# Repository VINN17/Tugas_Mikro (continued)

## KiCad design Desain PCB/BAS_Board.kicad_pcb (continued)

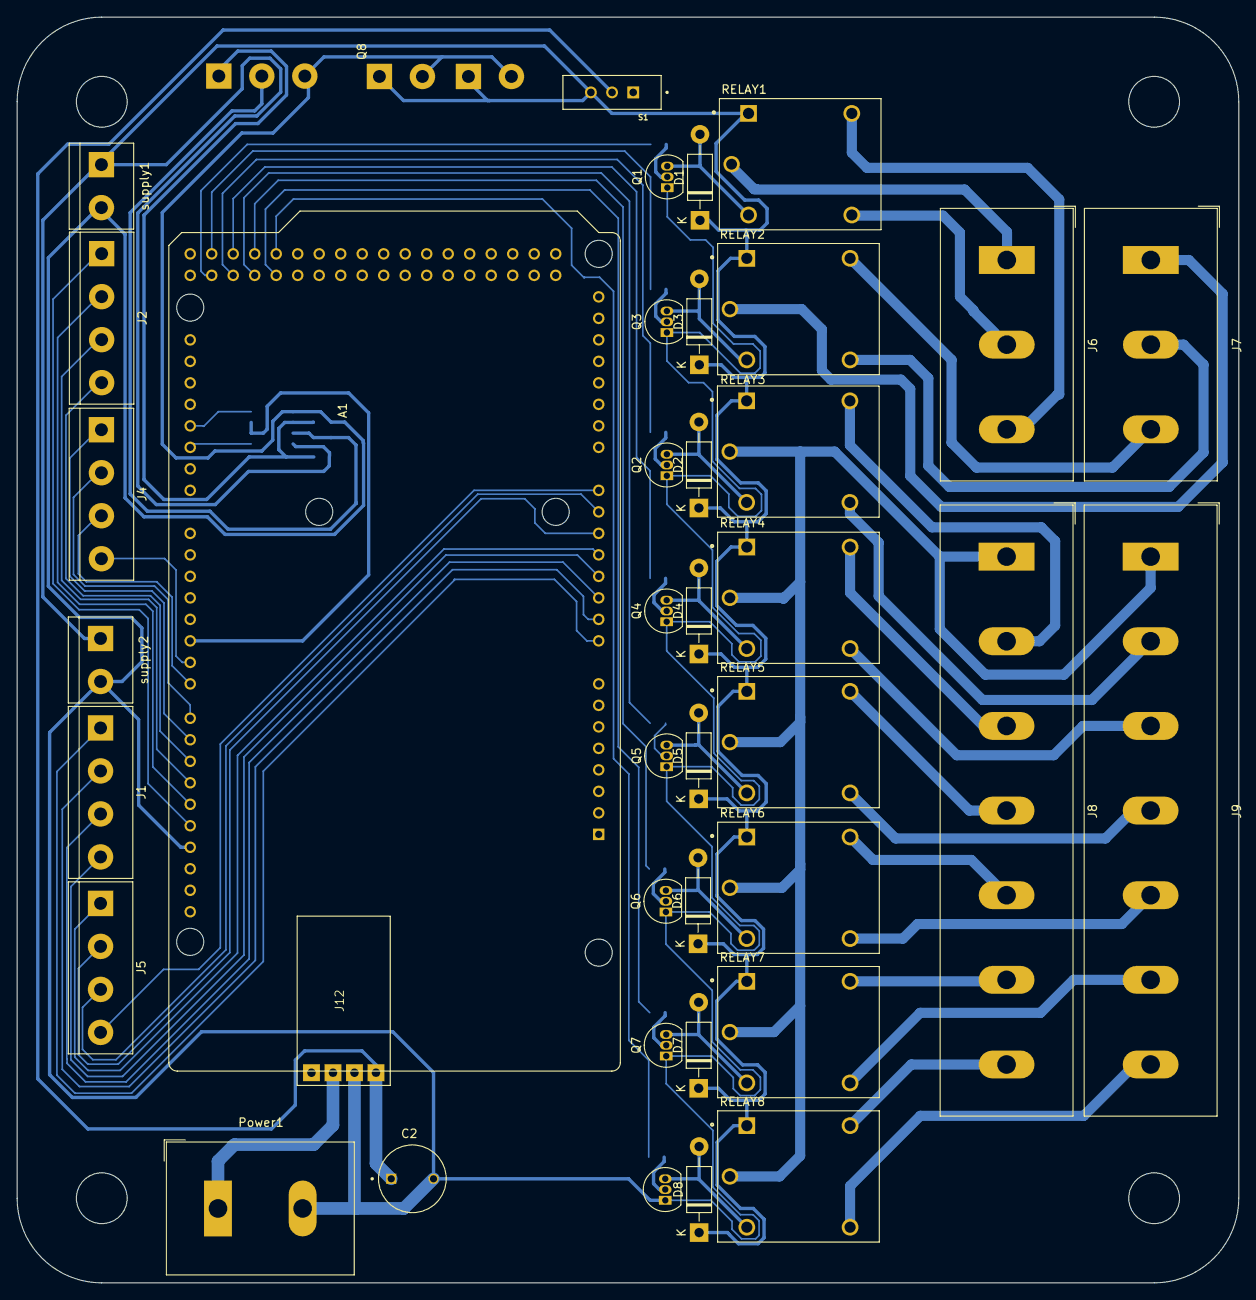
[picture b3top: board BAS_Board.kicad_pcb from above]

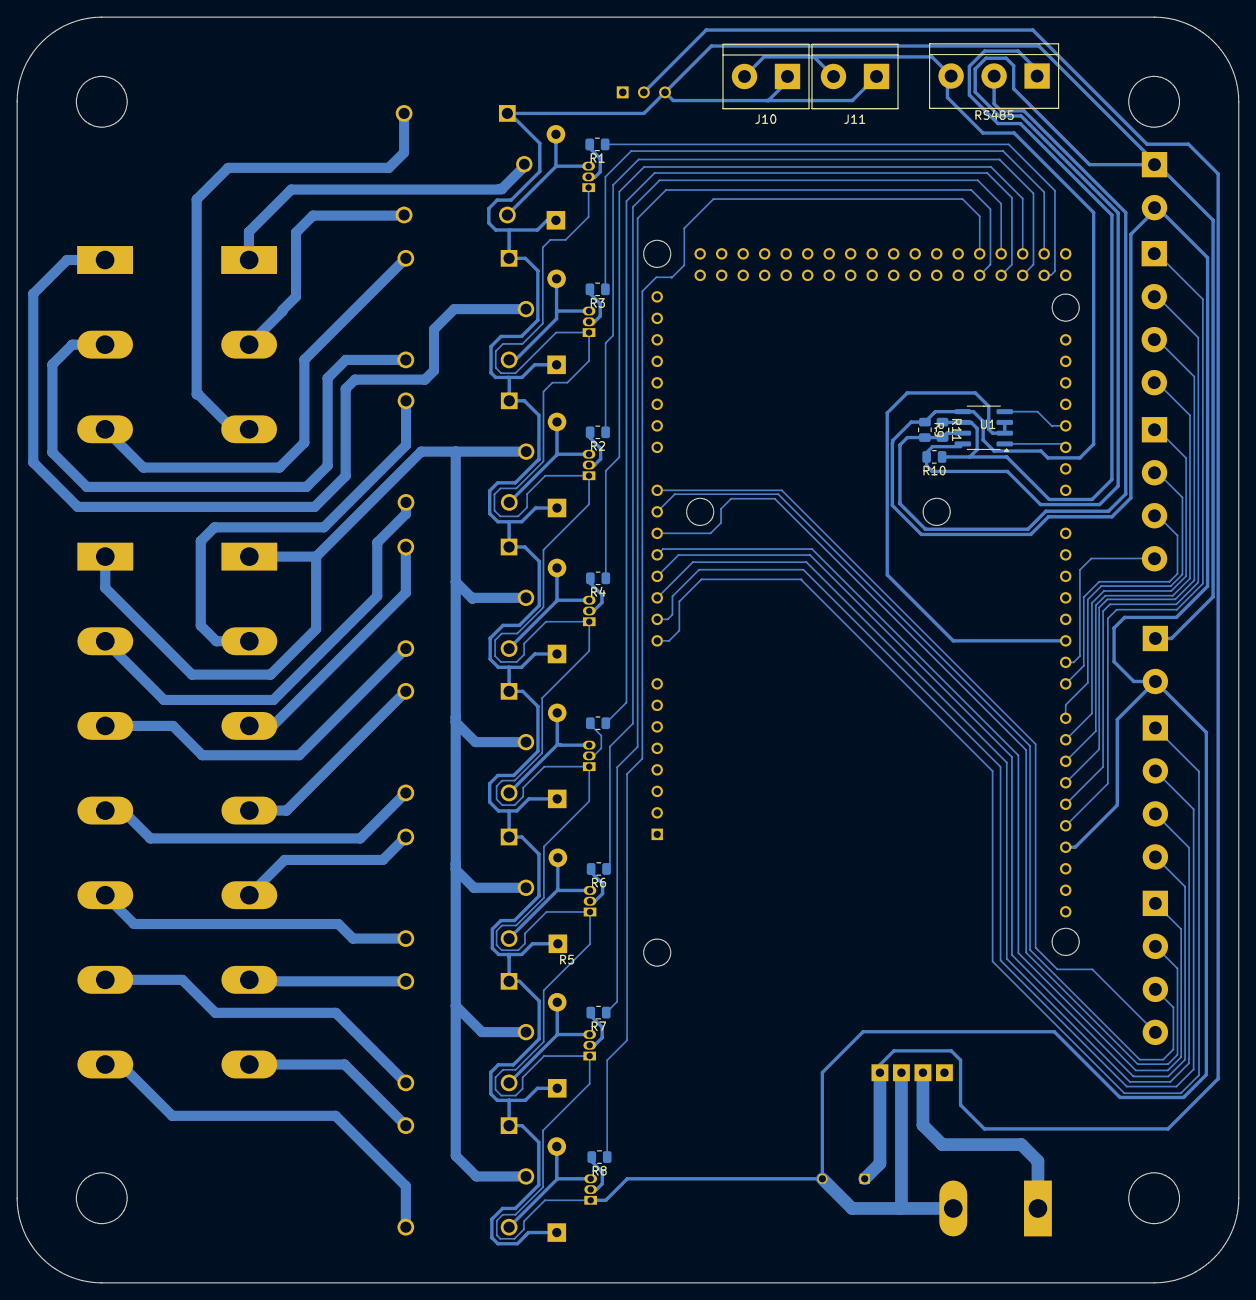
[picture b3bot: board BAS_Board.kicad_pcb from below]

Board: 2 copper layers, 144.3 x 149.5 mm, 54 parts (15 on the bottom side), 68 nets.

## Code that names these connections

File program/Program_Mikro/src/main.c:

#include <avr/interrupt.h>
#include <avr/io.h>
#include <stdio.h>
#include <stdlib.h>
#include <string.h>
#include <util/delay.h>

#define BAUD 115200
#define USE_DOUBLE_SPEED 1

#if USE_DOUBLE_SPEED
#define UBRR_VALUE ((F_CPU / (8UL * BAUD)) - 1)
#else
#define UBRR_VALUE ((F_CPU / (16UL * BAUD)) - 1)
#endif

volatile uint8_t adc_enabled = 0;
volatile uint8_t do_enabled = 0;
volatile uint8_t di_enabled = 0;
volatile uint8_t adc_looping = 0;
volatile uint8_t di_looping = 0;
volatile uint8_t adc_loop = 0;
volatile uint8_t di_loop = 0;

volatile uint16_t adc_values[5] = {0};
volatile uint8_t adc_channel = 0;

volatile uint8_t output_state[4] = {0};
volatile uint8_t digital_inputs[3] = {0};

char rx_buffer[32];
volatile uint8_t rx_index = 0;
uint8_t adc_request_channel = 0xFF;
uint8_t di_request_channel = 0xFF;
uint8_t do_request_channel = 0xFF;
uint8_t do_request_state = 0;

// USART Functions
void USART_Init(void) {
#if USE_DOUBLE_SPEED
  UCSR0A |= (1 << U2X0);
#else
  UCSR0A &= ~(1 << U2X0);
#endif
  UBRR0H = (unsigned char)(UBRR_VALUE >> 8);
  UBRR0L = (unsigned char)UBRR_VALUE;
  UCSR0B = (1 << RXEN0) | (1 << TXEN0) | (1 << RXCIE0);
  UCSR0C = (1 << UCSZ01) | (1 << UCSZ00);
}

void USART_Transmit(unsigned char data) {
  while (!(UCSR0A & (1 << UDRE0)));
  UDR0 = data;
}

void USART_SendString(const char* str) {
  while (*str) {
    USART_Transmit(*str++);
  }
}

// ADC
void ADC_Init() {
  ADMUX = (1 << REFS0);
  ADCSRA = (1 << ADEN) | (1 << ADPS2);
}

uint16_t ADC_Read(uint8_t channel) {
  ADMUX = (1 << REFS0) | (channel & 0x07);
  ADCSRA |= (1 << ADSC);
  while (ADCSRA & (1 << ADSC));
  return ADC;
}

// Timer
void Timer1_Init_100ms() {
  TCCR1A = 0;
  TCCR1B = (1 << WGM12) | (1 << CS12);
  OCR1A = 6250 - 1;
  TIMSK1 = (1 << OCIE1A);
}

ISR(TIMER1_COMPA_vect) {
  if (adc_enabled && (adc_loop || adc_request_channel < 5)) {
    for (uint8_t ch = 0; ch < 5; ch++) {
      if (adc_loop || adc_request_channel == ch) {
        uint16_t val = ADC_Read(ch);
        char buf[32];
        snprintf(buf, sizeof(buf), "ADC%d=%u\r\n", ch, val);
        USART_SendString(buf);
      }
    }
    adc_request_channel = 0xFF;
  }

  if (di_enabled && (di_loop || di_request_channel < 3)) {
    digital_inputs[0] = (PINB >> 1) & 1;
    digital_inputs[1] = (PINB >> 2) & 1;
    digital_inputs[2] = (PINB >> 3) & 1;

    for (uint8_t i = 0; i < 3; i++) {
      if (di_loop || di_request_channel == i) {
        char buf[16];
        snprintf(buf, sizeof(buf), "IN%d=%d\r\n", i, digital_inputs[i]);
        USART_SendString(buf);
      }
    }
    di_request_channel = 0xFF;
  }

  if (do_enabled) {
    // Terapkan status output berdasarkan output_state[]
    if (output_state[0])
      PORTD |= (1 << PD5);
    else
      PORTD &= ~(1 << PD5);  // OUT1
    if (output_state[1])
      PORTD |= (1 << PD6);
    else
      PORTD &= ~(1 << PD6);  // OUT2
    if (output_state[2])
      PORTD |= (1 << PD7);
    else
      PORTD &= ~(1 << PD7);  // OUT3
    if (output_state[3])
      PORTB |= (1 << PB0);
    else
      PORTB &= ~(1 << PB0);  // OUT4
  }
}

ISR(USART_RX_vect) {
  char c = UDR0;
  if (c == '\n' || c == '\r') {
    rx_buffer[rx_index] = '\0';

    if (strcmp(rx_buffer, "ADC_Set") == 0)
      adc_enabled = 1;
    else if (strcmp(rx_buffer, "DI_Set") == 0)
      di_enabled = 1;
    else if (strcmp(rx_buffer, "DO_Set") == 0)
      do_enabled = 1;
    else if (strncmp(rx_buffer, "ADC", 3) == 0 && rx_buffer[4] == '\0')
      adc_request_channel = rx_buffer[3] - '0';
    else if (strncmp(rx_buffer, "IN", 2) == 0 && rx_buffer[3] == '\0')
      di_request_channel = rx_buffer[2] - '0';

    else if (strncmp(rx_buffer, "OUT", 3) == 0 && rx_buffer[5] == '\0') {
      uint8_t out_index = rx_buffer[3] - '1';  // OUT1 → index 0
      if (out_index < 4) {
        output_state[out_index] = rx_buffer[4] - '0';  // '1' = ON, '0' = OFF
      }
    }

    rx_index = 0;
  } else {
    if (rx_index < sizeof(rx_buffer) - 1) {
      rx_buffer[rx_index++] = c;
    }
  }
  if (strcmp(rx_buffer, "ADC_Loop") == 0) {
    adc_looping = 1;
    adc_enabled = 1;
  } else if (strcmp(rx_buffer, "DI_Loop") == 0) {
    di_looping = 1;
    di_enabled = 1;
  } else if (strcmp(rx_buffer, "ADC_Stop") == 0) {
    adc_looping = 0;
  } else if (strcmp(rx_buffer, "DI_Stop") == 0) {
    di_looping = 0;
  }
  if (strcmp(rx_buffer, "ADC_Loop") == 0)
    adc_loop = 1;
  else if (strcmp(rx_buffer, "ADC_Stop") == 0)
    adc_loop = 0;
  else if (strcmp(rx_buffer, "DI_Loop") == 0)
    di_loop = 1;
  else if (strcmp(rx_buffer, "DI_Stop") == 0)
    di_loop = 0;
}

int main(void) {
  USART_Init();
  ADC_Init();
  Timer1_Init_100ms();

  DDRC = 0x00;                                      // ADC input PC0-PC4
  DDRB |= (1 << PB0);                               // output PB0
  DDRB &= ~((1 << PB1) | (1 << PB2) | (1 << PB3));  // input PB1-3
  DDRD |= (1 << PD5) | (1 << PD6) | (1 << PD7);     // output PD5-7

  sei();

  while (1) {
  }
}

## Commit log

2025-04-20 program
2025-05-05 3d design mekanik
2025-05-05 Revert "3d design mekanik"
2025-05-05 Create 3d Design
2025-05-05 3D Design
2025-05-05 Hapus folder 3d Design yang tidak sengaja terbuat
2025-05-25 add hardware
2025-05-25 UI/UX
2025-05-25 hardware
2025-05-25 main.c
2025-06-01 add_logo
2025-06-01 delete
2025-06-02 Create Desain PCB
2025-06-03 nontek
2025-06-12 add_delete
